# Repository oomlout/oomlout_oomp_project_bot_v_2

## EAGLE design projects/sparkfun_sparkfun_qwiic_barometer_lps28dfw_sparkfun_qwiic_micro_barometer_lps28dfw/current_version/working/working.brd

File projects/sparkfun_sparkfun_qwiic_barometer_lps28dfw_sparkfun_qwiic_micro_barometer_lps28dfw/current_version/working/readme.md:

# sparkfun_qwiic_barometer_lps28dfw
 
## summary 
* id: sparkfun_sparkfun_qwiic_barometer_lps28dfw_sparkfun_qwiic_micro_barometer_lps28dfw
* user: sparkfun
* name: sparkfun_qwiic_barometer_lps28dfw
* board: sparkfun_qwiic_micro_barometer_lps28dfw
* repo: https://github.com/sparkfun/SparkFun_Qwiic_Barometer_LPS28DFW

* src_file_repo_sch: 
* src_file_repo_sch_link: https://github.com/sparkfun/SparkFun_Qwiic_Barometer_LPS28DFW/tree/main/
* full details link: https://github.com/oomlout/oomlout_oomp_project_bot_v_2/tree/main/projects/sparkfun_sparkfun_qwiic_barometer_lps28dfw_sparkfun_qwiic_micro_barometer_lps28dfw/current_version/working

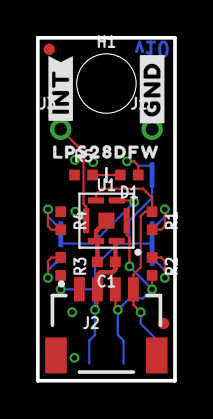
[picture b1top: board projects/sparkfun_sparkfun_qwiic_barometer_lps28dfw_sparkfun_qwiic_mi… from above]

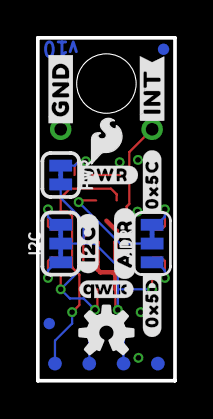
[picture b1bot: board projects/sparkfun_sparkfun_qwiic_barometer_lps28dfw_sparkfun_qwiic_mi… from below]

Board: 2 copper layers, 7.6 x 19.1 mm, 39 parts (19 on the bottom side), 12 nets.

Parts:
ADR: JUMPER-SMT_3_1-NC_TRACE_SILK; SMT-JUMPER_3_1-NC_TRACE_SILK
C1: 0.1uF; 0402-TIGHT
D1: RED; LED-0402
FD1, FD2, FD3, FD4: FIDUCIALUFIDUCIAL; FIDUCIAL-MICRO
FRAME1: FRAME-LETTER; CREATIVE_COMMONS
H1: STAND-OFF
I2C: JUMPER-SMT_3_2-NC_TRACE_SILK; SMT-JUMPER_3_2-NC_TRACE_SILK
J1, J3: 1X01_1MM_NO_SILK
J2: QWIIC_RIGHT_ANGLE; JST04_1MM_RA
LOGO1: OSHW-LOGOS; OSHW-LOGO-S
LOGO2: QWIIC_LOGO_3MM; QWIIC_3MM
LOGO3: SFE_LOGO_NAME_FLAMEBLANK; BLANK
PWR: JUMPER-SMT_2_NC_TRACE_SILK; SMT-JUMPER_2_NC_TRACE_SILK
R1, R2, R5: 2.2k; 0402-TIGHT
R3, R4: 10k; 0402-TIGHT
TP1, TP2, TP3, TP4: TEST-POINT3; PAD.03X.03
U1: LPS28DFW; CCLGA-7L
U$1, U$3: #INT#0
U$2, U$4: #GND#0
U$5: LPS28DFW0
U$6: SFE_LOGO_FLAME_.1
U$9: #I2C#0
U$10: #ADR#0
U$13: #PWR#0
U$16: #0X5D#0
U$17: #0X5C#0
U$19: ORDERING_INSTRUCTIONS

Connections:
3.3V: C1.1, I2C.2, J2.2, PWR.2, R3.2, TP2.1, U1.6
ADR: ADR.2, U1.2
GND: C1.2, J1.1, J2.1, R4.1, R5.1, TP1.1, U1.5, U1.7
INT: J3.1, U1.4
unnamed: D1.C, R5.2
unnamed: I2C.3, R1.2
unnamed: I2C.1, R2.1
unnamed: D1.A, PWR.1
unnamed: ADR.3, R4.2
unnamed: ADR.1, R3.1
SCL: J2.4, R1.1, TP4.1, U1.3
SDA: J2.3, R2.2, TP3.1, U1.1

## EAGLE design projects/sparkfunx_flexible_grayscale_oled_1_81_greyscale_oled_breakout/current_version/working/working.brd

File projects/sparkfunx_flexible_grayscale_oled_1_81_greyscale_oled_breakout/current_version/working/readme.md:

# flexible_grayscale_oled
 
## summary 
* id: sparkfunx_flexible_grayscale_oled_1_81_greyscale_oled_breakout
* user: sparkfunx
* name: flexible_grayscale_oled
* board: 1_81_greyscale_oled_breakout
* repo: https://github.com/sparkfunX/Flexible_Grayscale_OLED

* src_file_repo_sch: 
* src_file_repo_sch_link: https://github.com/sparkfunX/Flexible_Grayscale_OLED/tree/master/
* full details link: https://github.com/oomlout/oomlout_oomp_project_bot_v_2/tree/main/projects/sparkfunx_flexible_grayscale_oled_1_81_greyscale_oled_breakout/current_version/working

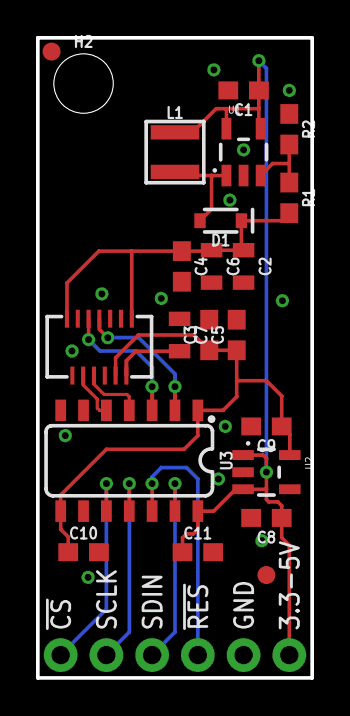
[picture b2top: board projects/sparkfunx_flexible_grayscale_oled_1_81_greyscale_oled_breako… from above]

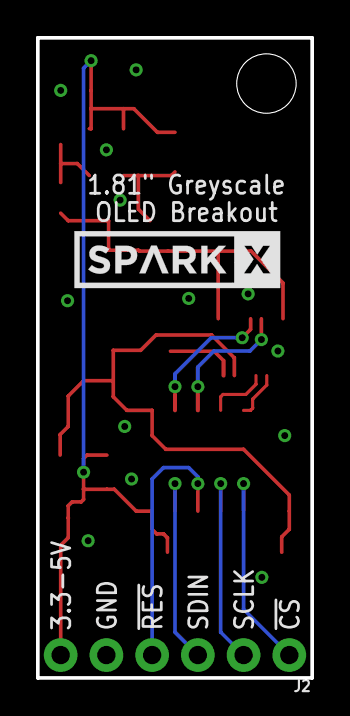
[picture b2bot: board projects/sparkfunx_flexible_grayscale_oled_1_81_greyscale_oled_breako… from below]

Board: 2 copper layers, 15.2 x 35.6 mm, 25 parts (3 on the bottom side), 15 nets.

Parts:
C1, C5, C8: 1.0uF; 0603
C2: 1.0uF/25V; 0805
C3, C10, C11: 0.1uF; 0603
C4: 0.1uF/25V; 0603
C6, C7: 2.2uF/25V; 0805
C9: 2.2uF; 0603
D1: 1A/23V/620mV; SOD-323
DS1: OEL_1.8OEL_Y3B; OEL_1.8_FPC_Y3B
FD1, FD2: FIDUCIAL1X2; FIDUCIAL-1X2
FRAME1: FRAME-LETTER; CREATIVE_COMMONS
H2: STAND-OFF
J2: 1X06_NO_SILK
L1: 10uH; INDUCTOR_3X3
LOGO1: SPARKX-LOGO5; SPARKX-LARGE
R1: 47k; 0603
R2: 5.6k; 0603
U1: AP3012; SOT23-5
U2: 3.3V; SOT23-5
U3: TXB0104; SO14

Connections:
3.3V: C3.1, C5.1, C9.1, C10.1, DS1.10, U2.5, U3.1, U3.8
12V: C2.1, C4.1, C6.1, D1.C, DS1.1, DS1.13, R1.2
!CS!: DS1.4, U3.5
!CS!_HIGH: J2.1, U3.10
!RES!: DS1.5, U3.3
!RES!_HIGH: J2.4, U3.12
GND: C1.2, C2.2, C3.2, C4.2, C5.2, C6.2, C7.1, C8.2, C9.2, C10.2, C11.2, DS1.2, DS1.3, DS1.8, DS1.9, J2.5, R2.1, U1.2, U2.2, U3.7
unnamed: C7.2, DS1.12
unnamed: D1.A, L1.P$2, U1.1
unnamed: R1.1, R2.2, U1.3
SCLK: DS1.6, U3.4
SCLK_HIGH: J2.2, U3.11
SDIN: DS1.7, U3.2
SDIN_HIGH: J2.3, U3.13
VIN: C1.1, C8.1, C11.1, J2.6, L1.P$1, U1.4, U1.5, U2.1, U2.3, U3.14

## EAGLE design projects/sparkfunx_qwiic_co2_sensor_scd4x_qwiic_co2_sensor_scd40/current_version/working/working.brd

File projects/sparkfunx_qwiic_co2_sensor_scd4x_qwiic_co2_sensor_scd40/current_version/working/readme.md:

# qwiic_co2_sensor_scd4x
 
## summary 
* id: sparkfunx_qwiic_co2_sensor_scd4x_qwiic_co2_sensor_scd40
* user: sparkfunx
* name: qwiic_co2_sensor_scd4x
* board: qwiic_co2_sensor_scd40
* repo: https://github.com/sparkfunX/Qwiic_CO2_Sensor-SCD4x

* src_file_repo_sch: 
* src_file_repo_sch_link: https://github.com/sparkfunX/Qwiic_CO2_Sensor-SCD4x/tree/main/
* full details link: https://github.com/oomlout/oomlout_oomp_project_bot_v_2/tree/main/projects/sparkfunx_qwiic_co2_sensor_scd4x_qwiic_co2_sensor_scd40/current_version/working

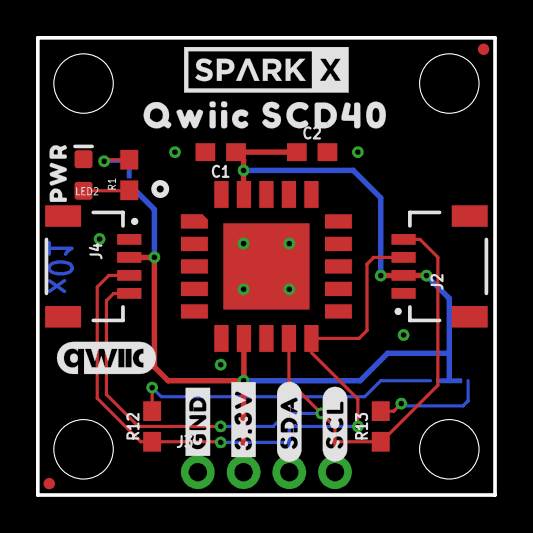
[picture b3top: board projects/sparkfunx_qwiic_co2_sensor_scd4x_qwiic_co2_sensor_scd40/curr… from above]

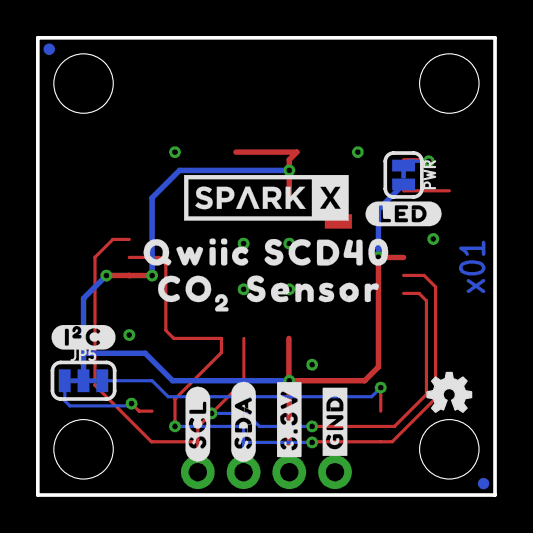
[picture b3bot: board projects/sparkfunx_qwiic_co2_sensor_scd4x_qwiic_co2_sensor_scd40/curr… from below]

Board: 2 copper layers, 25.4 x 25.4 mm, 43 parts (17 on the bottom side), 8 nets.

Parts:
C1: 0.1uF; 0603
C2: 4.7uF; 0603
FRAME1: FRAME-LETTER; CREATIVE_COMMONS
J2, J4: Qwiic Right Angle; JST04_1MM_RA
J3: PTH; 1X04_NO_SILK
JP5: SMT-JUMPER_3_2-NC_TRACE_SILK
JP21, JP61, JP71, JP81: FIDUCIALUFIDUCIAL; MICRO-FIDUCIAL
JP31, JP41, JP91, JP101: STAND-OFF
LED2: RED; LED-0603
LOGO1: OSHW-LOGOMINI; OSHW-LOGO-MINI
PWR: SMT-JUMPER_2_NC_TRACE_SILK
R1: 1k; 0603
R12, R13: 2.2k; 0603
U3: SCD4X
U$1: CO1
U$2, U$11: SCD400
U$3, U$4: QWIIC0
U$5, U$38: SPARKX-LOGO4; SPARKX-MEDIUM
U$6, U$34: #3#3V#0
U$7, U$35: #SDA#0
U$8, U$36: #SCL#0
U$9, U$33: #GND#0
U$10: #I�C#1
U$12: PWR0
U$13: SENSOR3
U$14: 20
U$23: #LED#0
U$42: QWIIC_5.5MM

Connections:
3.3V: C1.1, C2.1, J2.2, J3.2, J4.2, JP5.2, PWR.2, U3.7, U3.19
GND: C1.2, C2.2, J2.1, J3.1, J4.1, LED2.C, U3.6, U3.20, U3.CP
unnamed: JP5.1, R13.2
unnamed: LED2.A, R1.1
unnamed: JP5.3, R12.2
unnamed: PWR.1, R1.2
SCL: J2.4, J3.4, J4.4, R13.1, U3.9
SDA: J2.3, J3.3, J4.3, R12.1, U3.10

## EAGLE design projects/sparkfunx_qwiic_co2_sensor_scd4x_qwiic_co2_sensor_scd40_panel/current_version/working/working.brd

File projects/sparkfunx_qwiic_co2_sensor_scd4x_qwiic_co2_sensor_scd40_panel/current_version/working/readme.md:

# qwiic_co2_sensor_scd4x
 
## summary 
* id: sparkfunx_qwiic_co2_sensor_scd4x_qwiic_co2_sensor_scd40_panel
* user: sparkfunx
* name: qwiic_co2_sensor_scd4x
* board: qwiic_co2_sensor_scd40_panel
* repo: https://github.com/sparkfunX/Qwiic_CO2_Sensor-SCD4x

* src_file_repo_sch: 
* src_file_repo_sch_link: https://github.com/sparkfunX/Qwiic_CO2_Sensor-SCD4x/tree/main/
* full details link: https://github.com/oomlout/oomlout_oomp_project_bot_v_2/tree/main/projects/sparkfunx_qwiic_co2_sensor_scd4x_qwiic_co2_sensor_scd40_panel/current_version/working

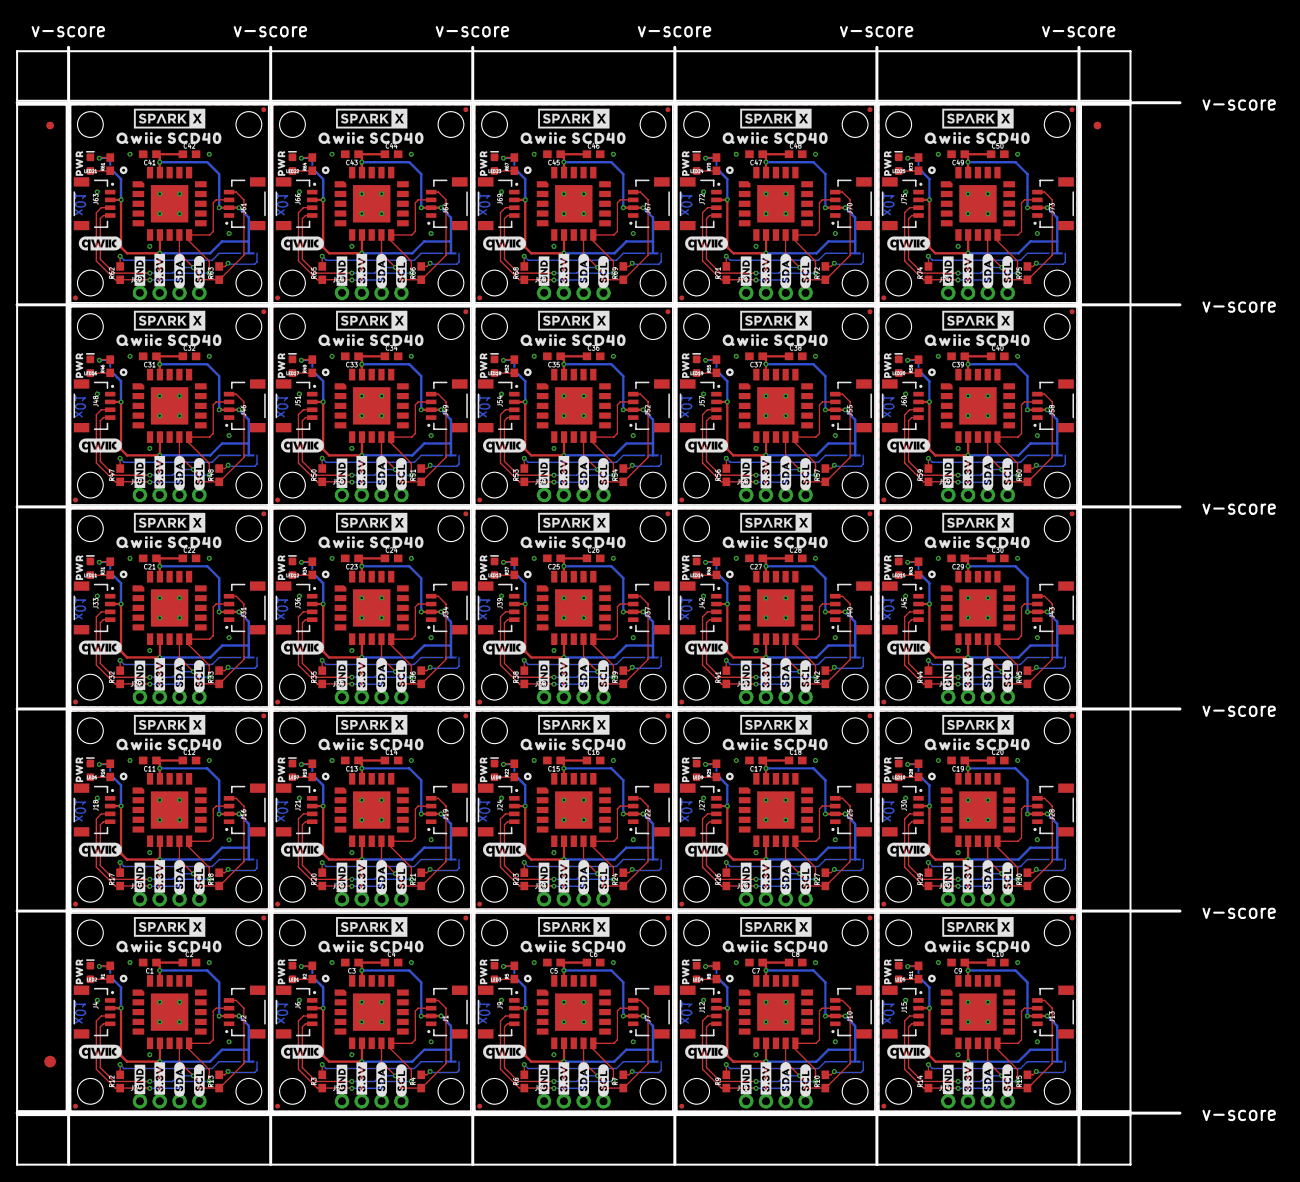
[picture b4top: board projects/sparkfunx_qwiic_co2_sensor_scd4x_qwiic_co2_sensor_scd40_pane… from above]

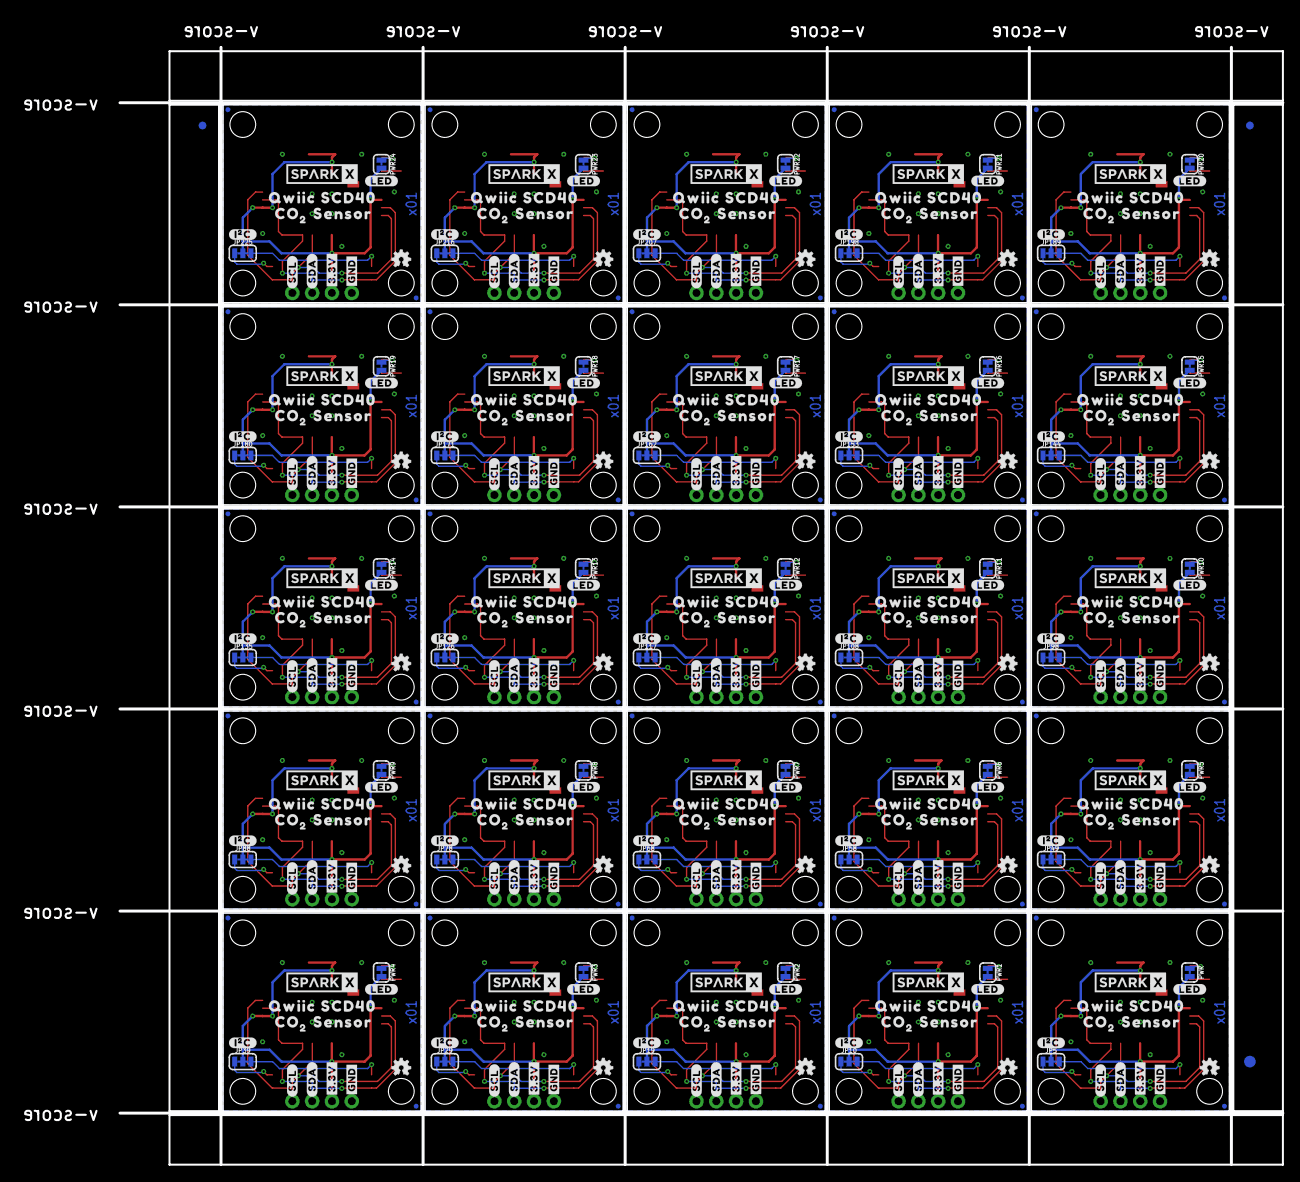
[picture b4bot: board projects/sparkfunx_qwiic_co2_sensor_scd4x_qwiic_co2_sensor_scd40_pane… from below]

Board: 2 copper layers, 149.1 x 143.3 mm, 1056 parts (428 on the bottom side), 200 nets.

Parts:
C1, C3, C5, C7, C9, C11, C13, C15, C17, C19, C21, C23, C25, C27, C29, C31, C33, C35, C37, C39, C41, C43, C45, C47, C49: 0.1uF; 0603
C2, C4, C6, C8, C10, C12, C14, C16, C18, C20, C22, C24, C26, C28, C30, C32, C34, C36, C38, C40, C42, C44, C46, C48, C50: 4.7uF; 0603
E$1, E$2, E$3, E$4: FIDUCIAL-1X2
E$5, E$6: FIDUCIAL-1.5X3
J1, J2, J4, J6, J7, J9, J10, J12, J13, J15, J16, J18, J19, J21, J22, J24, J25, J27, J28, J30, J31, J33, J34, J36, J37, J39, J40, J42, J43, J45, J46, J48, J49, J51, J52, J54, J55, J57, J58, J60, J61, J63, J64, J66, J67, J69, J70, J72, J73, J75: Qwiic Right Angle; JST04_1MM_RA
J3, J5, J8, J11, J14, J17, J20, J23, J26, J29, J32, J35, J38, J41, J44, J47, J50, J53, J56, J59, J62, J65, J68, J71, J74: PTH; 1X04_NO_SILK
JP1, JP2, JP8, JP9, JP11, JP12, JP17, JP18, JP20, JP22, JP27, JP28, JP30, JP31, JP32, JP37, JP38, JP40, JP41, JP42, JP47, JP48, JP50, JP51, JP56, JP57, JP59, JP60, JP66, JP67, JP69, JP70, JP76, JP77, JP79, JP80, JP86, JP87, JP89, JP90, JP91, JP96, JP97, JP99, JP100, JP101, JP106, JP107, JP109, JP110, JP115, JP116, JP118, JP119, JP124, JP125, JP127, JP128, JP133, JP134, JP136, JP137, JP142, JP143, JP145, JP146, JP151, JP152, JP154, JP155, JP160, JP161, JP163, JP164, JP169, JP170, JP172, JP173, JP178, JP179, JP181, JP182, JP187, JP188, JP190, JP191, JP196, JP197, JP199, JP200, JP205, JP206, JP208, JP209, JP214, JP215, JP217, JP218, JP223, JP224: STAND-OFF
JP3, JP4, JP6, JP7, JP13, JP14, JP15, JP16, JP21, JP23, JP24, JP25, JP26, JP33, JP34, JP35, JP36, JP43, JP44, JP45, JP46, JP52, JP53, JP54, JP55, JP61, JP62, JP63, JP64, JP65, JP71, JP72, JP73, JP74, JP75, JP81, JP82, JP83, JP84, JP85, JP92, JP93, JP94, JP95, JP102, JP103, JP104, JP105, JP111, JP112, JP113, JP114, JP120, JP121, JP122, JP123, JP129, JP130, JP131, JP132, JP138, JP139, JP140, JP141, JP147, JP148, JP149, JP150, JP156, JP157, JP158, JP159, JP165, JP166, JP167, JP168, JP174, JP175, JP176, JP177, JP183, JP184, JP185, JP186, JP192, JP193, JP194, JP195, JP201, JP202, JP203, JP204, JP210, JP211, JP212, JP213, JP219, JP220, JP221, JP222: FIDUCIALUFIDUCIAL; MICRO-FIDUCIAL
JP5, JP10, JP19, JP29, JP39, JP49, JP58, JP68, JP78, JP88, JP98, JP108, JP117, JP126, JP135, JP144, JP153, JP162, JP171, JP180, JP189, JP198, JP207, JP216, JP225: SMT-JUMPER_3_2-NC_TRACE_SILK
LED1, LED2, LED3, LED4, LED5, LED6, LED7, LED8, LED9, LED10, LED11, LED12, LED13, LED14, LED15, LED16, LED17, LED18, LED19, LED20, LED21, LED22, LED23, LED24, LED25: RED; LED-0603
LOGO1, LOGO2, LOGO3, LOGO4, LOGO5, LOGO6, LOGO7, LOGO8, LOGO9, LOGO10, LOGO11, LOGO12, LOGO13, LOGO14, LOGO15, LOGO16, LOGO17, LOGO18, LOGO19, LOGO20, LOGO21, LOGO22, LOGO23, LOGO24, LOGO25: OSHW-LOGOMINI; OSHW-LOGO-MINI
PWR, PWR1, PWR2, PWR3, PWR4, PWR5, PWR6, PWR7, PWR8, PWR9, PWR10, PWR11, PWR12, PWR13, PWR14, PWR15, PWR16, PWR17, PWR18, PWR19, PWR20, PWR21, PWR22, PWR23, PWR24: SMT-JUMPER_2_NC_TRACE_SILK
R1, R2, R5, R8, R11, R16, R19, R22, R25, R28, R31, R34, R37, R40, R43, R46, R49, R52, R55, R58, R61, R64, R67, R70, R73: 1k; 0603
R3, R4, R6, R7, R9, R10, R12, R13, R14, R15, R17, R18, R20, R21, R23, R24, R26, R27, R29, R30, R32, R33, R35, R36, R38, R39, R41, R42, R44, R45, R47, R48, R50, R51, R53, R54, R56, R57, R59, R60, R62, R63, R65, R66, R68, R69, R71, R72, R74, R75: 2.2k; 0603
U1, U2, U3, U4, U5, U6, U7, U8, U9, U10, U11, U12, U13, U14, U15, U16, U17, U18, U19, U20, U21, U22, U23, U24, U25: SCD4X
U$1, U$30, U$57, U$78, U$99, U$120, U$141, U$162, U$183, U$204, U$225, U$246, U$267, U$288, U$309, U$330, U$351, U$372, U$393, U$414, U$435, U$456, U$477, U$498, U$519: CO1
U$2, U$11, U$40, U$41, U$62, U$63, U$83, U$84, U$104, U$105, U$125, U$126, U$146, U$147, U$167, U$168, U$188, U$189, U$209, U$210, U$230, U$231, U$251, U$252, U$272, U$273, U$293, U$294, U$314, U$315, U$335, U$336, U$356, U$357, U$377, U$378, U$398, U$399, U$419, U$420, U$440, U$441, U$461, U$462, U$482, U$483, U$503, U$504, U$524, U$525: SCD400
U$3, U$4, U$31, U$32, U$58, U$59, U$79, U$80, U$100, U$101, U$121, U$122, U$142, U$143, U$163, U$164, U$184, U$185, U$205, U$206, U$226, U$227, U$247, U$248, U$268, U$269, U$289, U$290, U$310, U$311, U$331, U$332, U$352, U$353, U$373, U$374, U$394, U$395, U$415, U$416, U$436, U$437, U$457, U$458, U$478, U$479, U$499, U$500, U$520, U$521: QWIIC0
U$5, U$15, U$28, U$38, U$43, U$55, U$64, U$76, U$85, U$97, U$106, U$118, U$127, U$139, U$148, U$160, U$169, U$181, U$190, U$202, U$211, U$223, U$232, U$244, U$253, U$265, U$274, U$286, U$295, U$307, U$316, U$328, U$337, U$349, U$358, U$370, U$379, U$391, U$400, U$412, U$421, U$433, U$442, U$454, U$463, U$475, U$484, U$496, U$505, U$517: SPARKX-LOGO4; SPARKX-MEDIUM
U$6, U$16, U$19, U$34, U$44, U$47, U$65, U$68, U$86, U$89, U$107, U$110, U$128, U$131, U$149, U$152, U$170, U$173, U$191, U$194, U$212, U$215, U$233, U$236, U$254, U$257, U$275, U$278, U$296, U$299, U$317, U$320, U$338, U$341, U$359, U$362, U$380, U$383, U$401, U$404, U$422, U$425, U$443, U$446, U$464, U$467, U$485, U$488, U$506, U$509: #3#3V#0
U$7, U$17, U$20, U$35, U$45, U$48, U$66, U$69, U$87, U$90, U$108, U$111, U$129, U$132, U$150, U$153, U$171, U$174, U$192, U$195, U$213, U$216, U$234, U$237, U$255, U$258, U$276, U$279, U$297, U$300, U$318, U$321, U$339, U$342, U$360, U$363, U$381, U$384, U$402, U$405, U$423, U$426, U$444, U$447, U$465, U$468, U$486, U$489, U$507, U$510: #SDA#0
U$8, U$18, U$21, U$36, U$46, U$49, U$67, U$70, U$88, U$91, U$109, U$112, U$130, U$133, U$151, U$154, U$172, U$175, U$193, U$196, U$214, U$217, U$235, U$238, U$256, U$259, U$277, U$280, U$298, U$301, U$319, U$322, U$340, U$343, U$361, U$364, U$382, U$385, U$403, U$406, U$424, U$427, U$445, U$448, U$466, U$469, U$487, U$490, U$508, U$511: #SCL#0
U$9, U$22, U$24, U$33, U$50, U$51, U$71, U$72, U$92, U$93, U$113, U$114, U$134, U$135, U$155, U$156, U$176, U$177, U$197, U$198, U$218, U$219, U$239, U$240, U$260, U$261, U$281, U$282, U$302, U$303, U$323, U$324, U$344, U$345, U$365, U$366, U$386, U$387, U$407, U$408, U$428, U$429, U$449, U$450, U$470, U$471, U$491, U$492, U$512, U$513: #GND#0
U$10, U$25, U$52, U$73, U$94, U$115, U$136, U$157, U$178, U$199, U$220, U$241, U$262, U$283, U$304, U$325, U$346, U$367, U$388, U$409, U$430, U$451, U$472, U$493, U$514: #I�C#1
U$12, U$26, U$53, U$74, U$95, U$116, U$137, U$158, U$179, U$200, U$221, U$242, U$263, U$284, U$305, U$326, U$347, U$368, U$389, U$410, U$431, U$452, U$473, U$494, U$515: PWR0
U$13, U$37, U$60, U$81, U$102, U$123, U$144, U$165, U$186, U$207, U$228, U$249, U$270, U$291, U$312, U$333, U$354, U$375, U$396, U$417, U$438, U$459, U$480, U$501, U$522: SENSOR3
U$14, U$39, U$61, U$82, U$103, U$124, U$145, U$166, U$187, U$208, U$229, U$250, U$271, U$292, U$313, U$334, U$355, U$376, U$397, U$418, U$439, U$460, U$481, U$502, U$523: 20
U$23, U$27, U$54, U$75, U$96, U$117, U$138, U$159, U$180, U$201, U$222, U$243, U$264, U$285, U$306, U$327, U$348, U$369, U$390, U$411, U$432, U$453, U$474, U$495, U$516: #LED#0
U$29, U$42, U$56, U$77, U$98, U$119, U$140, U$161, U$182, U$203, U$224, U$245, U$266, U$287, U$308, U$329, U$350, U$371, U$392, U$413, U$434, U$455, U$476, U$497, U$518: QWIIC_5.5MM

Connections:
3.3V: C1.1, C2.1, J2.2, J3.2, J4.2, JP5.2, PWR.2, U3.7, U3.19
3.3V1: C3.1, C4.1, J1.2, J5.2, J6.2, JP10.2, PWR1.2, U1.7, U1.19
3.3V2: C5.1, C6.1, J7.2, J8.2, J9.2, JP19.2, PWR2.2, U2.7, U2.19
3.3V3: C7.1, C8.1, J10.2, J11.2, J12.2, JP29.2, PWR3.2, U4.7, U4.19
3.3V4: C9.1, C10.1, J13.2, J14.2, J15.2, JP39.2, PWR4.2, U5.7, U5.19
3.3V5: C11.1, C12.1, J16.2, J17.2, J18.2, JP49.2, PWR5.2, U6.7, U6.19
3.3V6: C13.1, C14.1, J19.2, J20.2, J21.2, JP58.2, PWR6.2, U7.7, U7.19
3.3V7: C15.1, C16.1, J22.2, J23.2, J24.2, JP68.2, PWR7.2, U8.7, U8.19
3.3V8: C17.1, C18.1, J25.2, J26.2, J27.2, JP78.2, PWR8.2, U9.7, U9.19
3.3V9: C19.1, C20.1, J28.2, J29.2, J30.2, JP88.2, PWR9.2, U10.7, U10.19
3.3V10: C21.1, C22.1, J31.2, J32.2, J33.2, JP98.2, PWR10.2, U11.7, U11.19
3.3V11: C23.1, C24.1, J34.2, J35.2, J36.2, JP108.2, PWR11.2, U12.7, U12.19
3.3V12: C25.1, C26.1, J37.2, J38.2, J39.2, JP117.2, PWR12.2, U13.7, U13.19
3.3V13: C27.1, C28.1, J40.2, J41.2, J42.2, JP126.2, PWR13.2, U14.7, U14.19
3.3V14: C29.1, C30.1, J43.2, J44.2, J45.2, JP135.2, PWR14.2, U15.7, U15.19
3.3V15: C31.1, C32.1, J46.2, J47.2, J48.2, JP144.2, PWR15.2, U16.7, U16.19
3.3V16: C33.1, C34.1, J49.2, J50.2, J51.2, JP153.2, PWR16.2, U17.7, U17.19
3.3V17: C35.1, C36.1, J52.2, J53.2, J54.2, JP162.2, PWR17.2, U18.7, U18.19
3.3V18: C37.1, C38.1, J55.2, J56.2, J57.2, JP171.2, PWR18.2, U19.7, U19.19
3.3V19: C39.1, C40.1, J58.2, J59.2, J60.2, JP180.2, PWR19.2, U20.7, U20.19
3.3V20: C41.1, C42.1, J61.2, J62.2, J63.2, JP189.2, PWR20.2, U21.7, U21.19
3.3V21: C43.1, C44.1, J64.2, J65.2, J66.2, JP198.2, PWR21.2, U22.7, U22.19
3.3V22: C45.1, C46.1, J67.2, J68.2, J69.2, JP207.2, PWR22.2, U23.7, U23.19
3.3V23: C47.1, C48.1, J70.2, J71.2, J72.2, JP216.2, PWR23.2, U24.7, U24.19
3.3V24: C49.1, C50.1, J73.2, J74.2, J75.2, JP225.2, PWR24.2, U25.7, U25.19
GND: C1.2, C2.2, J2.1, J3.1, J4.1, LED2.C, U3.6, U3.20, U3.CP
GND1: C3.2, C4.2, J1.1, J5.1, J6.1, LED1.C, U1.6, U1.20, U1.CP
GND2: C5.2, C6.2, J7.1, J8.1, J9.1, LED3.C, U2.6, U2.20, U2.CP
GND3: C7.2, C8.2, J10.1, J11.1, J12.1, LED4.C, U4.6, U4.20, U4.CP
GND4: C9.2, C10.2, J13.1, J14.1, J15.1, LED5.C, U5.6, U5.20, U5.CP
GND5: C11.2, C12.2, J16.1, J17.1, J18.1, LED6.C, U6.6, U6.20, U6.CP
GND6: C13.2, C14.2, J19.1, J20.1, J21.1, LED7.C, U7.6, U7.20, U7.CP
GND7: C15.2, C16.2, J22.1, J23.1, J24.1, LED8.C, U8.6, U8.20, U8.CP
GND8: C17.2, C18.2, J25.1, J26.1, J27.1, LED9.C, U9.6, U9.20, U9.CP
GND9: C19.2, C20.2, J28.1, J29.1, J30.1, LED10.C, U10.6, U10.20, U10.CP
GND10: C21.2, C22.2, J31.1, J32.1, J33.1, LED11.C, U11.6, U11.20, U11.CP
GND11: C23.2, C24.2, J34.1, J35.1, J36.1, LED12.C, U12.6, U12.20, U12.CP
GND12: C25.2, C26.2, J37.1, J38.1, J39.1, LED13.C, U13.6, U13.20, U13.CP
GND13: C27.2, C28.2, J40.1, J41.1, J42.1, LED14.C, U14.6, U14.20, U14.CP
GND14: C29.2, C30.2, J43.1, J44.1, J45.1, LED15.C, U15.6, U15.20, U15.CP
GND15: C31.2, C32.2, J46.1, J47.1, J48.1, LED16.C, U16.6, U16.20, U16.CP
GND16: C33.2, C34.2, J49.1, J50.1, J51.1, LED17.C, U17.6, U17.20, U17.CP
GND17: C35.2, C36.2, J52.1, J53.1, J54.1, LED18.C, U18.6, U18.20, U18.CP
GND18: C37.2, C38.2, J55.1, J56.1, J57.1, LED19.C, U19.6, U19.20, U19.CP
GND19: C39.2, C40.2, J58.1, J59.1, J60.1, LED20.C, U20.6, U20.20, U20.CP
GND20: C41.2, C42.2, J61.1, J62.1, J63.1, LED21.C, U21.6, U21.20, U21.CP
GND21: C43.2, C44.2, J64.1, J65.1, J66.1, LED22.C, U22.6, U22.20, U22.CP
GND22: C45.2, C46.2, J67.1, J68.1, J69.1, LED23.C, U23.6, U23.20, U23.CP
GND23: C47.2, C48.2, J70.1, J71.1, J72.1, LED24.C, U24.6, U24.20, U24.CP
GND24: C49.2, C50.2, J73.1, J74.1, J75.1, LED25.C, U25.6, U25.20, U25.CP
unnamed: LED1.A, R2.1
unnamed: PWR1.1, R2.2
unnamed: JP10.1, R4.2
unnamed: JP10.3, R3.2
unnamed: LED3.A, R5.1
unnamed: PWR2.1, R5.2
unnamed: JP19.1, R7.2
unnamed: JP19.3, R6.2
unnamed: JP5.1, R13.2
unnamed: LED2.A, R1.1
unnamed: LED4.A, R8.1
unnamed: PWR3.1, R8.2
unnamed: JP29.1, R10.2
unnamed: JP29.3, R9.2
unnamed: JP5.3, R12.2
unnamed: LED5.A, R11.1
unnamed: PWR.1, R1.2
unnamed: PWR4.1, R11.2
unnamed: JP39.1, R15.2
unnamed: JP39.3, R14.2
unnamed: LED6.A, R16.1
unnamed: PWR5.1, R16.2
unnamed: JP49.1, R18.2
unnamed: JP49.3, R17.2
unnamed: LED7.A, R19.1
unnamed: PWR6.1, R19.2
unnamed: JP58.1, R21.2
unnamed: JP58.3, R20.2
unnamed: LED8.A, R22.1
unnamed: PWR7.1, R22.2
unnamed: JP68.1, R24.2
unnamed: JP68.3, R23.2
unnamed: LED9.A, R25.1
unnamed: PWR8.1, R25.2
unnamed: JP78.1, R27.2
unnamed: JP78.3, R26.2
unnamed: LED10.A, R28.1
unnamed: PWR9.1, R28.2
unnamed: JP88.1, R30.2
unnamed: JP88.3, R29.2
unnamed: LED11.A, R31.1
unnamed: PWR10.1, R31.2
unnamed: JP98.1, R33.2
unnamed: JP98.3, R32.2
unnamed: LED12.A, R34.1
unnamed: PWR11.1, R34.2
unnamed: JP108.1, R36.2
unnamed: JP108.3, R35.2
unnamed: LED13.A, R37.1
unnamed: PWR12.1, R37.2
unnamed: JP117.1, R39.2
unnamed: JP117.3, R38.2
unnamed: LED14.A, R40.1
unnamed: PWR13.1, R40.2
unnamed: JP126.1, R42.2
unnamed: JP126.3, R41.2
unnamed: LED15.A, R43.1
unnamed: PWR14.1, R43.2
unnamed: JP135.1, R45.2
unnamed: JP135.3, R44.2
unnamed: LED16.A, R46.1
unnamed: PWR15.1, R46.2
unnamed: JP144.1, R48.2
unnamed: JP144.3, R47.2
unnamed: LED17.A, R49.1
unnamed: PWR16.1, R49.2
unnamed: JP153.1, R51.2
unnamed: JP153.3, R50.2
unnamed: LED18.A, R52.1
unnamed: PWR17.1, R52.2
unnamed: JP162.1, R54.2
unnamed: JP162.3, R53.2
unnamed: LED19.A, R55.1
unnamed: PWR18.1, R55.2
unnamed: JP171.1, R57.2
unnamed: JP171.3, R56.2
unnamed: LED20.A, R58.1
unnamed: PWR19.1, R58.2
unnamed: JP180.1, R60.2
unnamed: JP180.3, R59.2
unnamed: LED21.A, R61.1
unnamed: PWR20.1, R61.2
unnamed: JP189.1, R63.2
unnamed: JP189.3, R62.2
unnamed: LED22.A, R64.1
unnamed: PWR21.1, R64.2
unnamed: JP198.1, R66.2
unnamed: JP198.3, R65.2
unnamed: LED23.A, R67.1
unnamed: PWR22.1, R67.2
unnamed: JP207.1, R69.2
unnamed: JP207.3, R68.2
unnamed: LED24.A, R70.1
unnamed: PWR23.1, R70.2
unnamed: JP216.1, R72.2
unnamed: JP216.3, R71.2
unnamed: LED25.A, R73.1
unnamed: PWR24.1, R73.2
unnamed: JP225.1, R75.2
unnamed: JP225.3, R74.2
SCL: J2.4, J3.4, J4.4, R13.1, U3.9
SCL1: J1.4, J5.4, J6.4, R4.1, U1.9
SCL2: J7.4, J8.4, J9.4, R7.1, U2.9
SCL3: J10.4, J11.4, J12.4, R10.1, U4.9
SCL4: J13.4, J14.4, J15.4, R15.1, U5.9
SCL5: J16.4, J17.4, J18.4, R18.1, U6.9
SCL6: J19.4, J20.4, J21.4, R21.1, U7.9
SCL7: J22.4, J23.4, J24.4, R24.1, U8.9
SCL8: J25.4, J26.4, J27.4, R27.1, U9.9
SCL9: J28.4, J29.4, J30.4, R30.1, U10.9
SCL10: J31.4, J32.4, J33.4, R33.1, U11.9
SCL11: J34.4, J35.4, J36.4, R36.1, U12.9
SCL12: J37.4, J38.4, J39.4, R39.1, U13.9
SCL13: J40.4, J41.4, J42.4, R42.1, U14.9
SCL14: J43.4, J44.4, J45.4, R45.1, U15.9
SCL15: J46.4, J47.4, J48.4, R48.1, U16.9
SCL16: J49.4, J50.4, J51.4, R51.1, U17.9
SCL17: J52.4, J53.4, J54.4, R54.1, U18.9
SCL18: J55.4, J56.4, J57.4, R57.1, U19.9
SCL19: J58.4, J59.4, J60.4, R60.1, U20.9
SCL20: J61.4, J62.4, J63.4, R63.1, U21.9
SCL21: J64.4, J65.4, J66.4, R66.1, U22.9
SCL22: J67.4, J68.4, J69.4, R69.1, U23.9
SCL23: J70.4, J71.4, J72.4, R72.1, U24.9
SCL24: J73.4, J74.4, J75.4, R75.1, U25.9
SDA: J2.3, J3.3, J4.3, R12.1, U3.10
SDA1: J1.3, J5.3, J6.3, R3.1, U1.10
SDA2: J7.3, J8.3, J9.3, R6.1, U2.10
SDA3: J10.3, J11.3, J12.3, R9.1, U4.10
SDA4: J13.3, J14.3, J15.3, R14.1, U5.10
SDA5: J16.3, J17.3, J18.3, R17.1, U6.10
SDA6: J19.3, J20.3, J21.3, R20.1, U7.10
SDA7: J22.3, J23.3, J24.3, R23.1, U8.10
SDA8: J25.3, J26.3, J27.3, R26.1, U9.10
SDA9: J28.3, J29.3, J30.3, R29.1, U10.10
SDA10: J31.3, J32.3, J33.3, R32.1, U11.10
SDA11: J34.3, J35.3, J36.3, R35.1, U12.10
SDA12: J37.3, J38.3, J39.3, R38.1, U13.10
SDA13: J40.3, J41.3, J42.3, R41.1, U14.10
SDA14: J43.3, J44.3, J45.3, R44.1, U15.10
SDA15: J46.3, J47.3, J48.3, R47.1, U16.10
SDA16: J49.3, J50.3, J51.3, R50.1, U17.10
SDA17: J52.3, J53.3, J54.3, R53.1, U18.10
SDA18: J55.3, J56.3, J57.3, R56.1, U19.10
SDA19: J58.3, J59.3, J60.3, R59.1, U20.10
SDA20: J61.3, J62.3, J63.3, R62.1, U21.10
SDA21: J64.3, J65.3, J66.3, R65.1, U22.10
SDA22: J67.3, J68.3, J69.3, R68.1, U23.10
SDA23: J70.3, J71.3, J72.3, R71.1, U24.10
SDA24: J73.3, J74.3, J75.3, R74.1, U25.10

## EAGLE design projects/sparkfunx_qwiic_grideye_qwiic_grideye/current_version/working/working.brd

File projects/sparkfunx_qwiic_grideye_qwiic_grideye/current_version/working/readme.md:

# qwiic_grideye
 
## summary 
* id: sparkfunx_qwiic_grideye_qwiic_grideye
* user: sparkfunx
* name: qwiic_grideye
* board: qwiic_grideye
* repo: https://github.com/sparkfunX/Qwiic_GridEye

* src_file_repo_sch: 
* src_file_repo_sch_link: https://github.com/sparkfunX/Qwiic_GridEye/tree/master/
* full details link: https://github.com/oomlout/oomlout_oomp_project_bot_v_2/tree/main/projects/sparkfunx_qwiic_grideye_qwiic_grideye/current_version/working

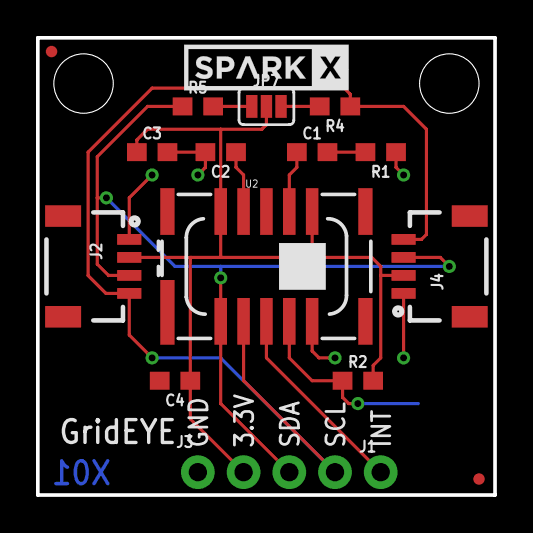
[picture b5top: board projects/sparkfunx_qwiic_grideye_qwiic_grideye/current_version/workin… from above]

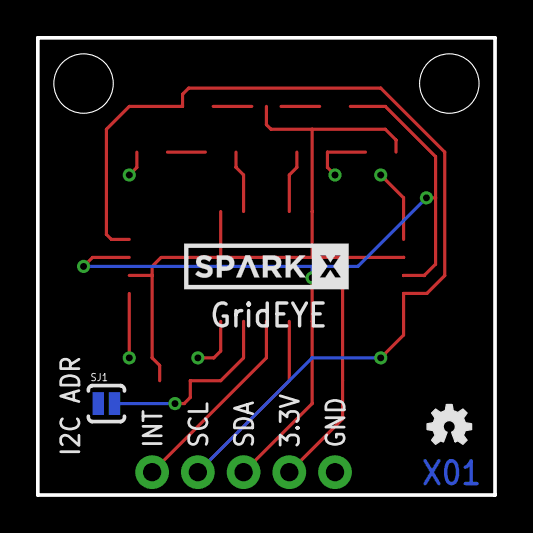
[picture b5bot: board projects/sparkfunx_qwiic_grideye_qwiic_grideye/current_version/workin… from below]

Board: 2 copper layers, 25.4 x 25.4 mm, 23 parts (3 on the bottom side), 11 nets.

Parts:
C1: 1.0uF; 0603
C2: 2.2uF; 0603
C3: 10uF; 0603
C4: 0.1uF; 0603
FRAME1: FRAME-LETTER; CREATIVE_COMMONS
J1: 1X01_NO_SILK
J2, J4: SMD; 1X04_1MM_RA
J3: PTH; 1X04_NO_SILK
JP2, JP6: FIDUCIALUFIDUCIAL; MICRO-FIDUCIAL
JP3, JP4: STAND-OFF
JP7: SMT-JUMPER_3_2-NC_PASTE_SILK
LOGO1: OSHW-LOGOMINI; OSHW-LOGO-MINI
R1: 20; 0603
R2: 10k; 0603
R4, R5: 4.7k; 0603
SJ1: SJ_2S-NO
U2: GRIDEYE; GRIDEYE-AMG88
U$1, U$2: SPARKX-LOGO4; SPARKX-MEDIUM

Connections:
3.3V: C3.1, C4.1, J2.2, J3.2, J4.2, JP7.2, R2.2, U2.9, U2.13
ADDR: R2.1, SJ1.2, U2.5
GND: C2.2, C3.2, C4.2, J2.1, J3.1, J4.1, R1.1, SJ1.1, U2.6
INT: J1.1, U2.4
unnamed: JP7.1, R5.2
unnamed: JP7.3, R4.2
unnamed: C2.1, U2.12
unnamed: C1.1, U2.10
unnamed: C1.2, R1.2
SCL: J2.4, J3.4, J4.4, R4.1, U2.3
SDA: J2.3, J3.3, J4.3, R5.1, U2.2

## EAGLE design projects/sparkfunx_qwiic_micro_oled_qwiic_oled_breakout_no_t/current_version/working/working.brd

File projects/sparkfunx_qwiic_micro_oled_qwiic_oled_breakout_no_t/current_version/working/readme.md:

# qwiic_micro_oled
 
## summary 
* id: sparkfunx_qwiic_micro_oled_qwiic_oled_breakout_no_t
* user: sparkfunx
* name: qwiic_micro_oled
* board: qwiic_oled_breakout_no_t
* repo: https://github.com/sparkfunX/Qwiic_Micro_OLED

* src_file_repo_sch: 
* src_file_repo_sch_link: https://github.com/sparkfunX/Qwiic_Micro_OLED/tree/master/
* full details link: https://github.com/oomlout/oomlout_oomp_project_bot_v_2/tree/main/projects/sparkfunx_qwiic_micro_oled_qwiic_oled_breakout_no_t/current_version/working

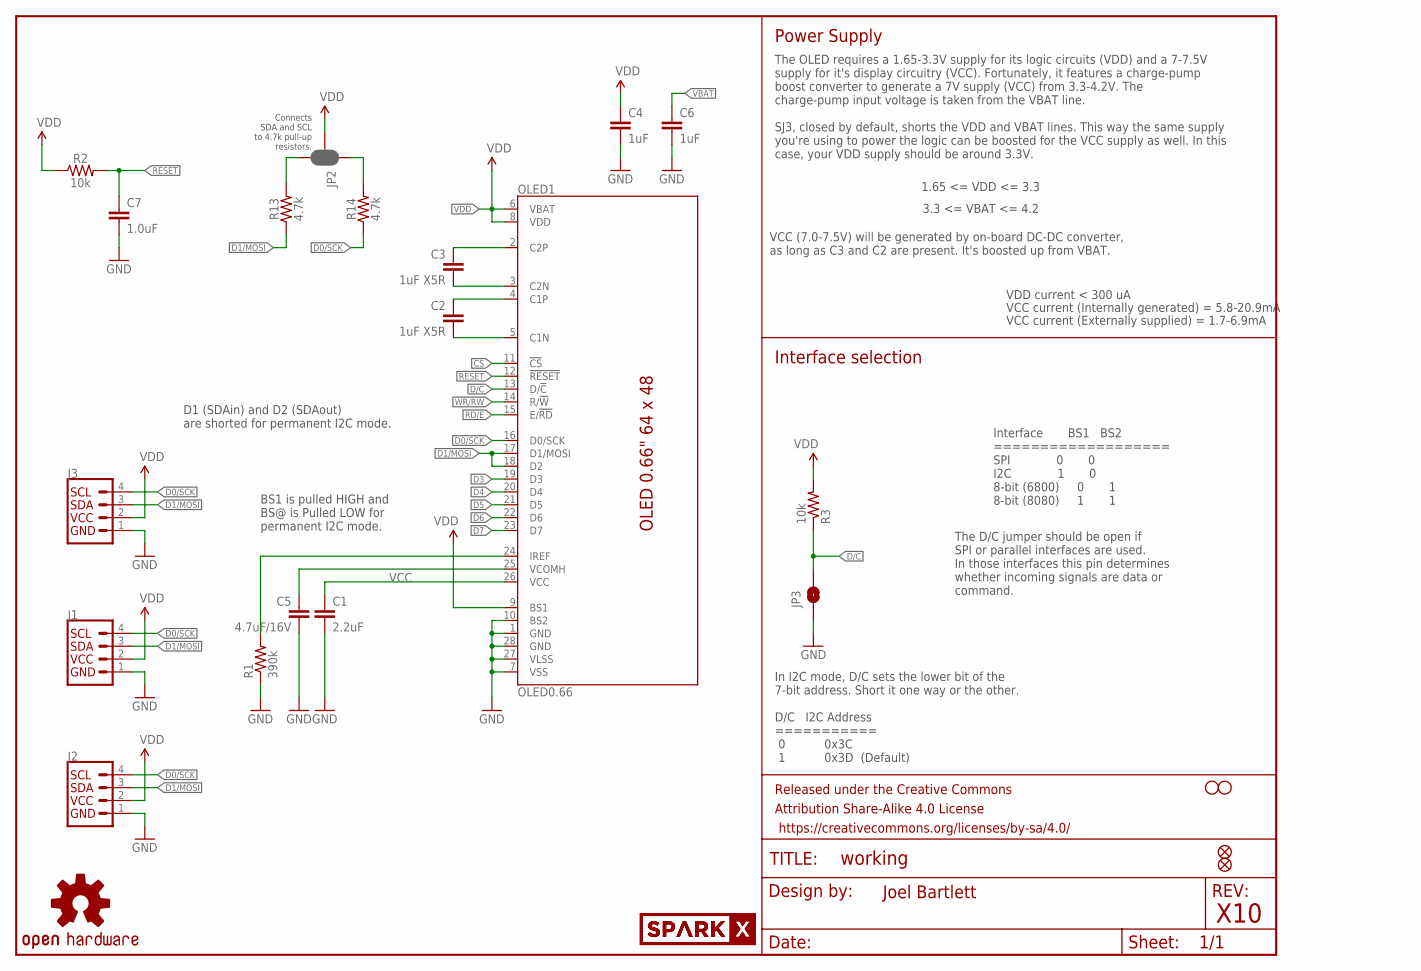
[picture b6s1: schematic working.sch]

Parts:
C1: 2.2uF; 0805
C2, C3: 1uF X5R; 0805
C4, C6: 1uF; 0603-CAP
C5: 4.7uF/16V; 1206
C7: 1.0uF; 0603
FID1, FID2: FIDUCIAL1X2; FIDUCIAL-1X2
FRAME1: FRAME-LETTER; CREATIVE_COMMONS
H1, H2: STAND-OFF
J1, J2: I2C_STANDARDJS-1MM; 1X04_1MM_RA
J3: I2C_STANDARD_NO_SILK; 1X04_NO_SILK
JP2: JUMPER-SMT_3_2-NC_PASTE_SILK; SMT-JUMPER_3_2-NC_PASTE_SILK
JP3: JUMPER-SMT_2_NO_SILK; SMT-JUMPER_2_NO_SILK
LOGO3: OSHW-LOGOS; OSHW-LOGO-S
OLED1: OLED0.66; OLED-0.66-64X48
R1: 390k; 0603-RES
R2: 10k; 0603
R3: 10k; 0603-RES
R13, R14: 4.7k; 0603
U$1: SPARKX-LOGO4; SPARKX-MEDIUM
U$3: SPARKX-LOGO2; SPARKX-TINY

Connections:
C1N: C2.2, OLED1.5 (C1N)
C1P: C2.1, OLED1.4 (C1P)
C2N: C3.2, OLED1.3 (C2N)
C2P: C3.1, OLED1.2 (C2P)
CS: OLED1.11 (!CS!)
D0/SCK: J1.4 (SCL), J2.4 (SCL), J3.4 (SCL), OLED1.16 (D0/SCK), R14.1
D1/MOSI: J1.3 (SDA), J2.3 (SDA), J3.3 (SDA), OLED1.17 (D1/MOSI), OLED1.18 (D2), R13.1
D3: OLED1.19 (D3)
D4: OLED1.20 (D4)
D5: OLED1.21 (D5)
D6: OLED1.22 (D6)
D7: OLED1.23 (D7)
D/C: JP3.2, OLED1.13 (D/!C!), R3.1
GND: C1.2, C4.2, C5.2, C6.2, C7.2, J1.1 (GND), J2.1 (GND), J3.1 (GND), JP3.1, OLED1.1 (GND), OLED1.7 (VSS), OLED1.10 (BS2), OLED1.27 (VLSS), OLED1.28 (GND), R1.1
IREF: OLED1.24 (IREF), R1.2
unnamed: JP2.3, R13.2
unnamed: JP2.1, R14.2
RD/E: OLED1.15 (E/!RD!)
RESET: C7.1, OLED1.12 (!RESET!), R2.2
VBAT: C6.1
VCC: C1.1, OLED1.26 (VCC)
VCOMH: C5.1, OLED1.25 (VCOMH)
VDD: C4.1, J1.2 (VCC), J2.2 (VCC), J3.2 (VCC), JP2.2, OLED1.6 (VBAT), OLED1.8 (VDD), OLED1.9 (BS1), R2.1, R3.2
WR/RW: OLED1.14 (R/!W!)

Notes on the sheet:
X10
1.65 <= VDD <= 3.3
VDD current < 300 uA
VCC current (Internally generated) = 5.8-20.9mA
VCC current (Externally supplied) = 1.7-6.9mA
Interface BS1 BS2 =================== SPI 0 0 I2C 1 0 8-bit (6800) 0 1 8-bit (8080) 1 1
VCC (7.0-7.5V) will be generated by on-board DC-DC converter, as long as C3 and C2 are present. It's boosted up from VBAT.
3.3 <= VBAT <= 4.2
Interface selection
D1 (SDAin) and D2 (SDAout) are shorted for permanent I2C mode.
In I2C mode, D/C sets the lower bit of the 7-bit address. Short it one way or the other. D/C I2C Address =========== 0 0x3C 1 0x3D (Default)
Power Supply
The OLED requires a 1.65-3.3V supply for its logic circuits (VDD) and a 7-7.5V supply for it's display circuitry (VCC). Fortunately, it features a charge-pump boost converter to generate a 7V supply (VCC) from 3.3-4.2V. The charge-pump input voltage is taken from the VBAT line. SJ3, closed by defau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
The D/C jumper should be open if SPI or parallel interfaces are used. In those interfaces this pin determines whether incoming signals are data or command.
BS1 is pulled HIGH and BS@ is Pulled LOW for permanent I2C mode.
Connects SDA and SCL to 4.7k pull-up resistors.
Joel Bartlett

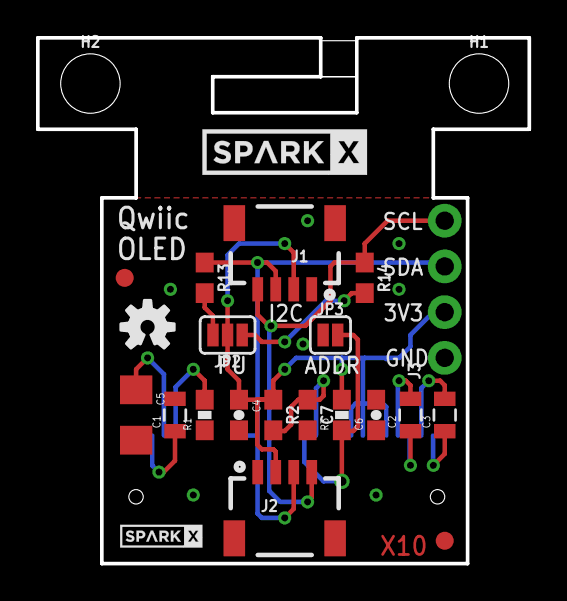
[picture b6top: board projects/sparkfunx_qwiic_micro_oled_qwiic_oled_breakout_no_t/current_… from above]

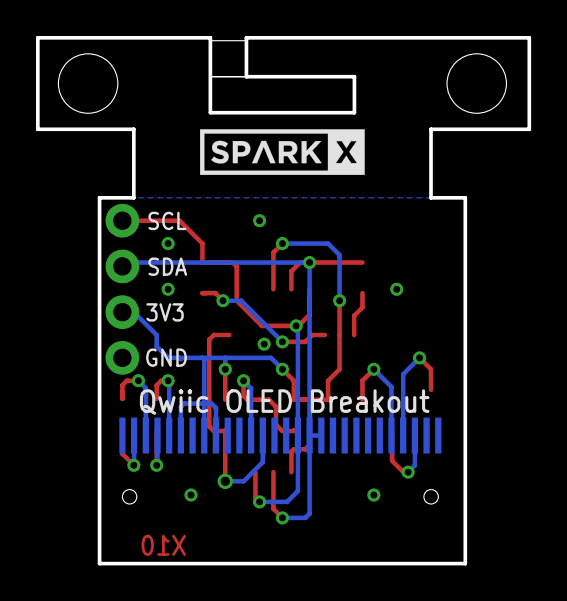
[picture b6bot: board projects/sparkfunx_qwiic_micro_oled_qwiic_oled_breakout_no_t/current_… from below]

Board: 2 copper layers, 27.3 x 29.2 mm, 27 parts (2 on the bottom side), 15 nets.

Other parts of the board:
U$2: SPARKX-LOGO4; SPARKX-MEDIUM

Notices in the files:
parts and their libraries:
SparkFun-Aesthetics: Licensing: Creative Commons ShareAlike 4.0 International - https://creativecommons.org/licenses/by-sa/4.0
SparkFun-Aesthetics: Released under the Creative Commons Attribution Share-Alike 4.0 License
SparkFun-Aesthetics: https://creativecommons.org/licenses/by-sa/4.0
